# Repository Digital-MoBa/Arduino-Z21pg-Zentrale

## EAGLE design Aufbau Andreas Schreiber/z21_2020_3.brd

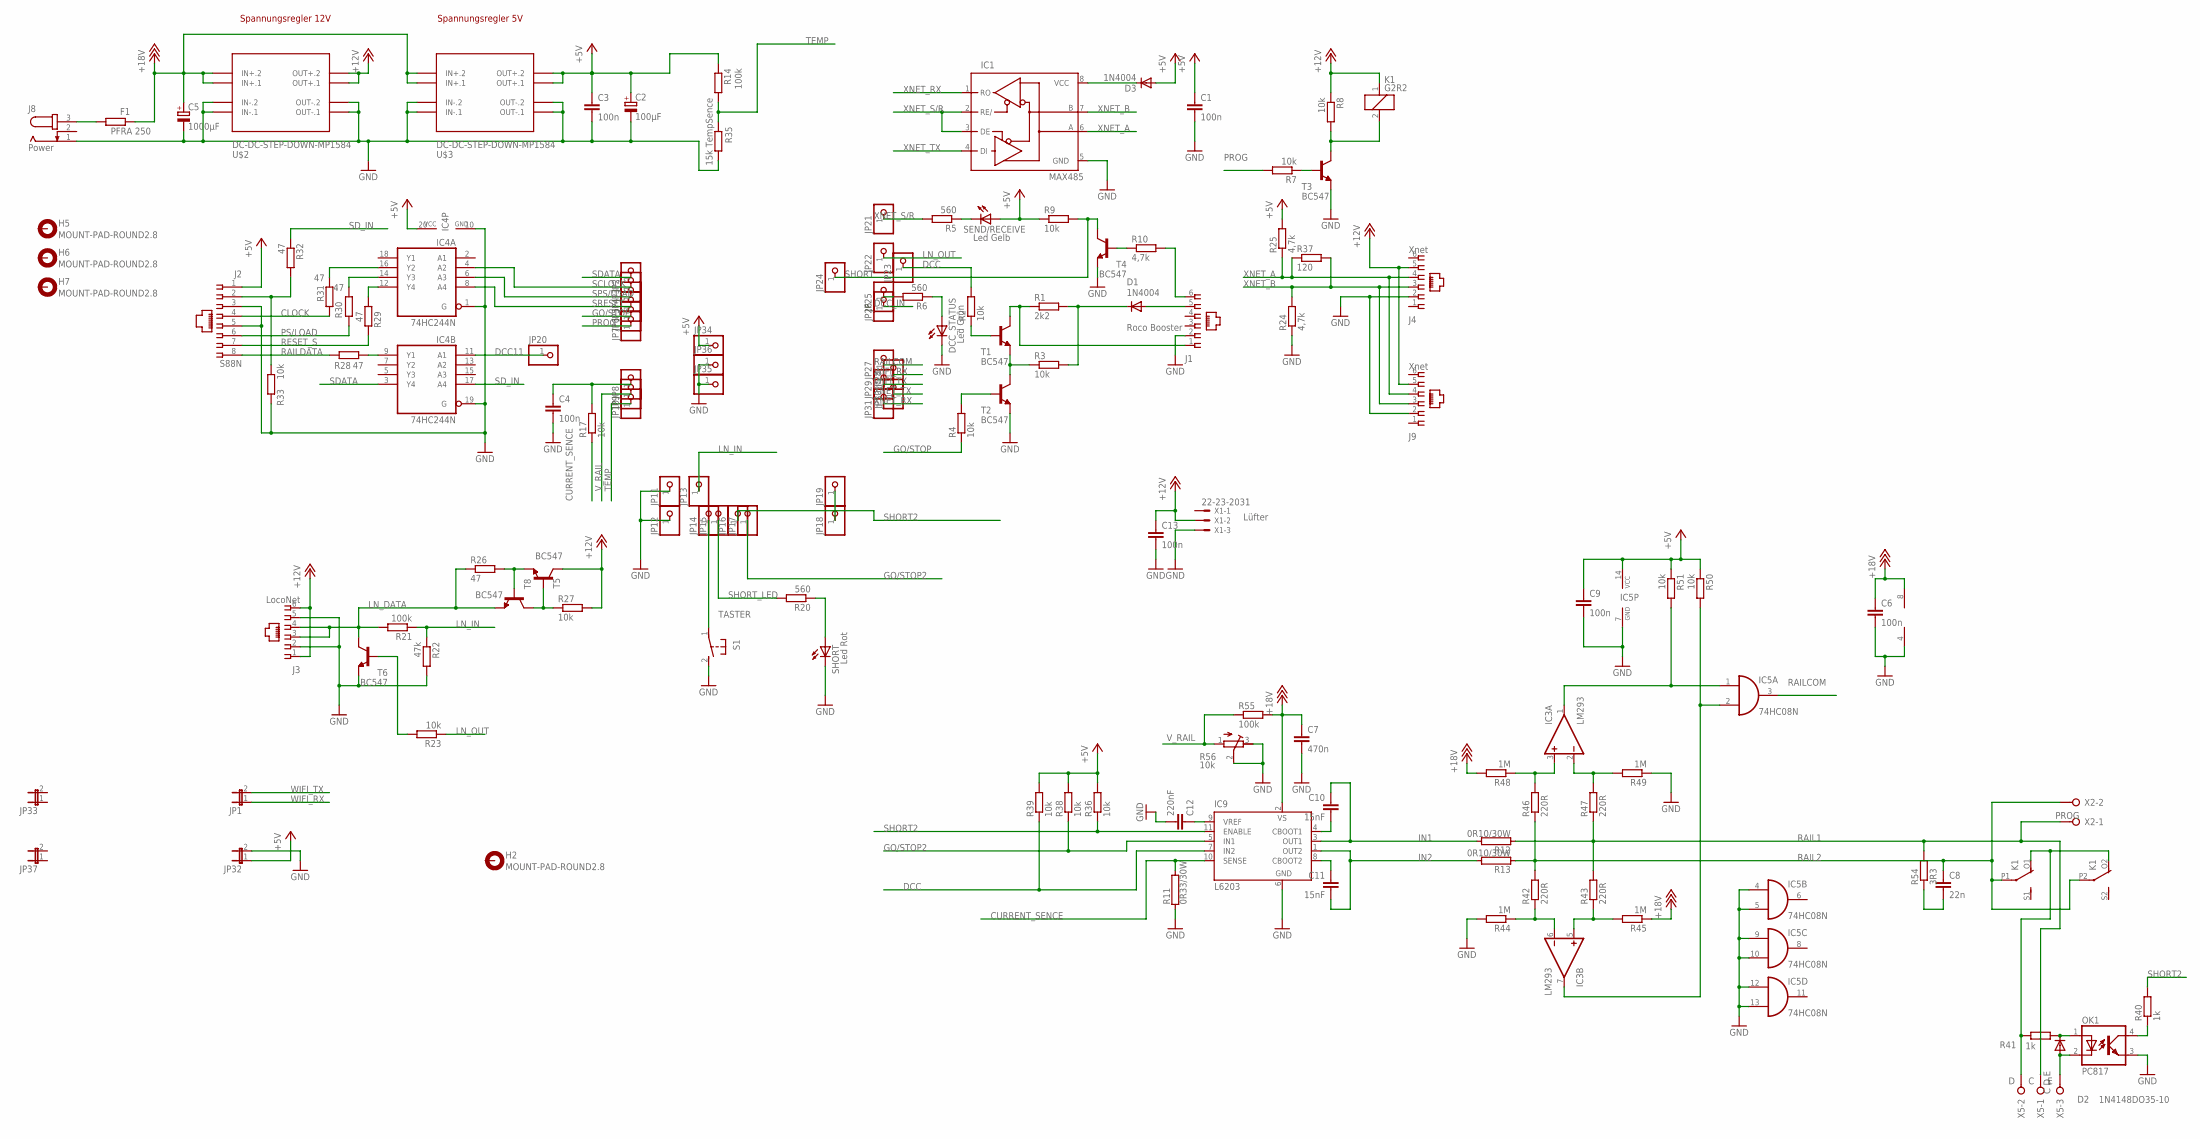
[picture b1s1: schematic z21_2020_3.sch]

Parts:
C1, C3, C4, C6, C9, C13: 100n; C050-024X044
C2: 100µF; E3,5-10
C5: 1000µF; E5-13
C7: 470n; C050-024X044
C8: 22n; C050-024X044
C10, C11: 15nF; C050-025X075
C12: 220nF; C050-025X075
D1, D3: 1N4004; DO41-10
D2: 1N4148DO35-10; DO35-10
DCC_STATUS: Led Grün; LD260
F1: PFRA 250; 0204/5
H2, H5, H6, H7: MOUNT-PAD-ROUND2.8; 2,8-PAD
IC1: MAX485; DIL08
IC3: LM293; DIL08
IC4: 74HC244N; DIL20
IC5: 74HC08N; DIL14
IC9: L6203; MULTIWATT-11
J1: Roco Booster; 520250-3
J2: S88N; 520251-4
J3: LocoNet; 520250-3
J4, J9: Xnet; 520250-3
J8: Power; SPC4077
JP1, JP32, JP33, JP37: JP1E; JP1
JP2, JP3, JP4, JP5, JP6, JP7, JP8, JP9, JP10, JP11, JP12, JP13, JP14, JP15, JP16, JP17, JP18, JP19, JP20, JP21, JP22, JP23, JP24, JP25, JP26, JP27, JP28, JP29, JP30, JP31, JP34, JP35, JP36: PINHD-1X1; 1X01
K1: G2R2
OK1: PC817; DIL04
R1: 2k2; 0204/7
R2: 10k; 0204/7
R3, R7, R8, R9, R17, R23, R27, R33, R36, R38, R39, R50, R51: 10k; 0207/10
R4: 10k; 0207/15
R5, R6, R20: 560; 0204/7
R10: 4,7k; 0204/7
R11: 0R33/30W; MNS-2
R12, R13: 0R10/30W; MNS-2
R14, R21: 100k; 0207/10
R22: 47k; 0207/10
R24, R25: 4,7k; 0207/10
R26: 47; 0204/7
R28, R29, R30, R31, R32: 47; 0207/10
R35: 15k TempSence; 0204/7
R37: 120; 0207/10
R40, R41: 1k; 0207/10
R42, R43, R46, R47: 220R; 0207/10
R44, R45, R48, R49: 1M; 0207/10
R54: 3R3; 0204/7
R55: 100k; 0207/12
R56: 10k; RTRIM64X
S1: 31-XX; B3F-31XX
SEND/RECEIVE: Led Gelb; LD260
SHORT: Led Rot; LD260
T1, T2, T3, T4, T5, T6, T8: BC547; TO92
U$2, U$3: DC-DC-STEP-DOWN-MP1584
X1: 22-23-2031
X2: PROG; W237-132
X5: C D E; W237-3E

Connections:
+5V: C1.1, C2.+, C3.1, C9.1, D3.A, IC4.20 (VCC), IC5.14 (VCC), J2.1, JP32.1, JP34.1, R9.1, R14.1, R25.2, R36.2, R38.2, R39.2, R50.1, R51.1, SEND/RECEIVE.A, U$3.OUT+.1, U$3.OUT+.2
+12V: C13.1, J3.1, J3.6, J4.5, J9.5, K1.1, R8.1, R27.2, T5.3 (C), U$2.OUT+.1, U$2.OUT+.2, X1.2
+18V: C5.+, C6.1, C7.1, F1.1, IC3.8 (V+), IC9.2 (VS), R45.1, R48.2, R55.2, U$2.IN+.1, U$2.IN+.2, U$3.IN+.1, U$3.IN+.2
CLOCK: J2.4, R31.2
CURRENT_SENCE: IC9.10 (SENSE), R11.2, R17.1
DCC: IC9.7 (IN2), JP23.1, R2.2, R39.1
DCC11: IC4.11 (A1), JP20.1
DCC_IN: JP26.1
GND: C1.2, C2.-, C3.2, C4.2, C5.-, C6.2, C7.2, C9.2, C12.2, C13.2, DCC_STATUS.K (C), IC1.5 (GND), IC3.4 (V-), IC4.1 (G), IC4.10 (GND), IC4.19 (G), IC5.4 (I0), IC5.5 (I1), IC5.7 (GND), IC5.9 (I0), IC5.10 (I1), IC5.12 (I0), IC5.13 (I1), IC9.6 (GND), J1.2, J2.3, J2.5, J3.2, J3.5, J4.2, J8.1, J9.2, JP11.1, JP12.1, JP32.2, JP35.1, JP36.1, OK1.3 (EMIT), R11.1, R22.2, R24.1, R33.2, R35.2, R44.2, R49.1, R56.2 (S), R56.3 (E), S1.2 (S), SHORT.K (C), T2.1 (E), T3.1 (E), T4.1 (E), T6.1 (E), U$2.IN-.1, U$2.IN-.2, U$2.OUT-.1, U$2.OUT-.2, U$3.IN-.1, U$3.IN-.2, U$3.OUT-.1, U$3.OUT-.2, X1.3
GO/STOP: JP6.1, R4.1
GO/STOP2: IC9.5 (IN1), JP17.1, R38.1
IN1: C10.1, IC9.3 (OUT1), R12.2
IN2: C11.2, IC9.1 (OUT2), R13.2
LN_DATA: J3.3, J3.4, R21.2, R26.1, T6.3 (C), T8.1 (E)
LN_IN: JP13.1, R21.1, R22.1
LN_OUT: JP22.1, R23.1
unnamed: J1.6, R10.2
unnamed: D1.C, R1.2, R3.2
unnamed: D1.A, J1.5
unnamed: R2.1, T1.2 (B)
unnamed: R3.1, T1.1 (E), T2.3 (C)
unnamed: J1.1, R1.1, T1.3 (C)
unnamed: JP25.1, R6.2
unnamed: F1.2, J8.3
unnamed: R4.2, T2.2 (B)
unnamed: DCC_STATUS.A, R6.1
unnamed: R5.1, SEND/RECEIVE.K (C)
unnamed: D3.C, IC1.8 (VCC)
unnamed: K1.2, R8.2, T3.3 (C)
unnamed: R7.1, T3.2 (B)
unnamed: R10.1, T4.2 (B)
unnamed: JP18.1, JP19.1
unnamed: R20.1, SHORT.A
unnamed: C4.1, JP8.1, R17.2
unnamed: K1.O1 (O), K1.O2 (O), R41.2, X5.2
unnamed: D2.C, OK1.1 (A), R41.1
unnamed: R26.2, T5.1 (E), T8.2 (B)
unnamed: R23.2, T6.2 (B)
unnamed: D2.A, OK1.2 (C), X5.3
unnamed: R27.1, T5.2 (B), T8.3 (C)
unnamed: IC4.9 (Y1), R28.2
unnamed: IC4.14 (Y3), R30.1
unnamed: IC4.16 (Y2), R31.1
unnamed: IC4.12 (Y4), R29.1
unnamed: IC3.6 (-IN), R42.1, R44.1
unnamed: J2.2, R32.2, R33.1
unnamed: IC3.5 (+IN), R43.1, R45.2
unnamed: IC3.7 (OUT), IC5.2 (I1), R50.2
unnamed: IC3.3 (+IN), R46.2, R48.1
unnamed: IC3.2 (-IN), R47.2, R49.2
unnamed: OK1.4 (COL), R40.1
unnamed: IC3.1 (OUT), IC5.1 (I0), R51.2
unnamed: C10.2, IC9.4 (CBOOT1)
unnamed: C8.2, R54.1
unnamed: C11.1, IC9.8 (CBOOT2)
unnamed: C12.1, IC9.9 (VREF)
PROG: JP7.1, R7.2
PS/LOAD: J2.6, R30.2
RAIL1: R12.1, R43.2, R47.1, R54.2, X2.1, X5.1
RAIL2: C8.1, K1.P1, K1.P2, R13.1, R42.2, R46.1, X2.2
RAILCOM: IC5.3 (O), JP27.1
RAILDATA: J2.8, R28.1
RESET_S: J2.7, R29.2
SCLOCK: IC4.4 (A2), JP3.1
SDATA: IC4.3 (Y4), JP2.1
SD_IN: IC4.17 (A4), R32.1
SHORT: JP24.1, R9.2, T4.3 (C)
SHORT2: IC9.11 (ENABLE), JP16.1, R36.1, R40.2
SHORT_LED: JP15.1, R20.2
SPS/LOAD: IC4.6 (A3), JP4.1
SRESET: IC4.8 (A4), JP5.1
TASTER: JP14.1, S1.1
TEMP: JP10.1, R14.2, R35.1
V_RAIL: JP9.1, R55.1, R56.1 (A)
WIFI_RX: JP1.1, JP28.1
WIFI_TX: JP1.2, JP29.1
XNET_A: IC1.6 (A), J4.4, J9.4, R25.1, R37.1
XNET_B: IC1.7 (B), J4.3, J9.3, R24.2, R37.2
XNET_RX: IC1.1 (RO), JP31.1
XNET_S/R: IC1.2 (RE/), IC1.3 (DE), JP21.1, R5.2
XNET_TX: IC1.4 (DI), JP30.1

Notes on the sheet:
Spannungsregler 12V
Spannungsregler 5V
D C E
Lüfter

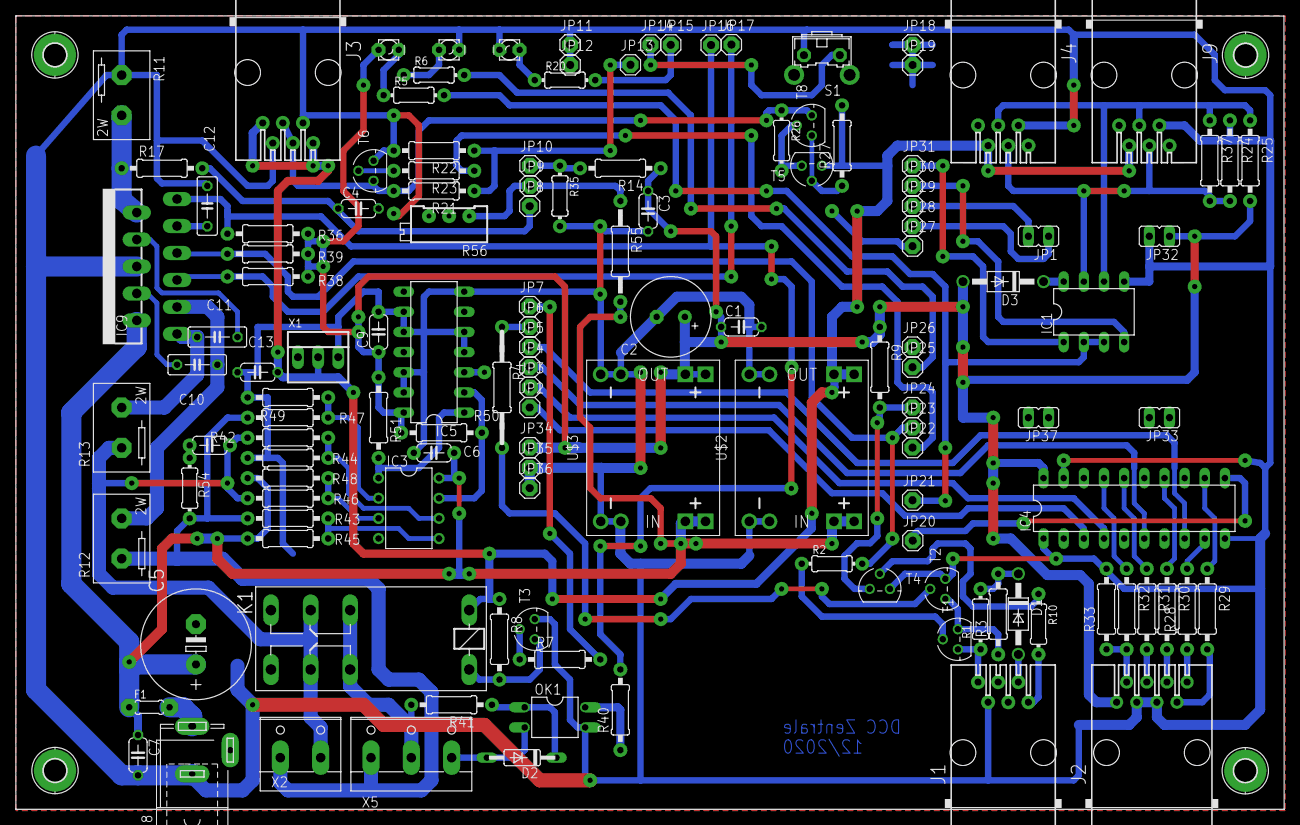
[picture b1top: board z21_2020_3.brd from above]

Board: 2 copper layers, 159.9 x 100.0 mm, 136 parts (0 on the bottom side), 80 nets.

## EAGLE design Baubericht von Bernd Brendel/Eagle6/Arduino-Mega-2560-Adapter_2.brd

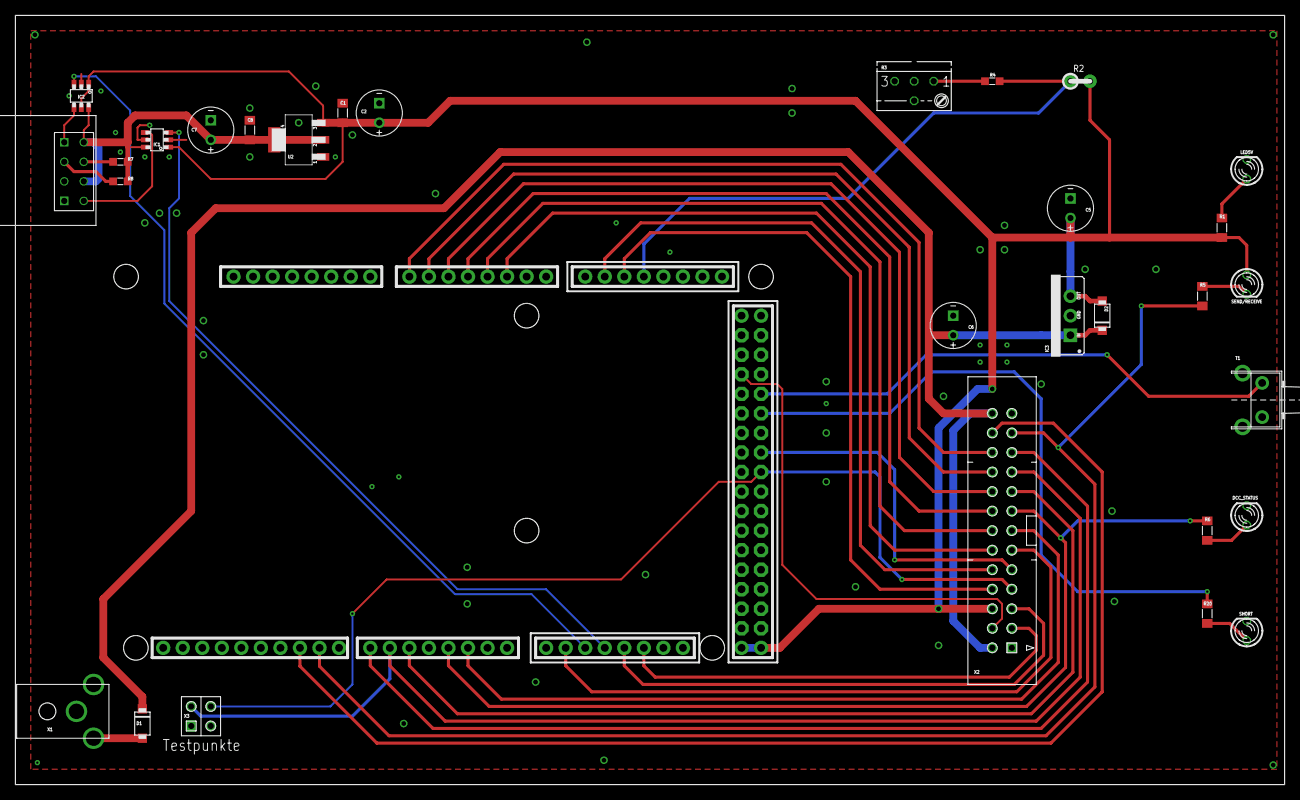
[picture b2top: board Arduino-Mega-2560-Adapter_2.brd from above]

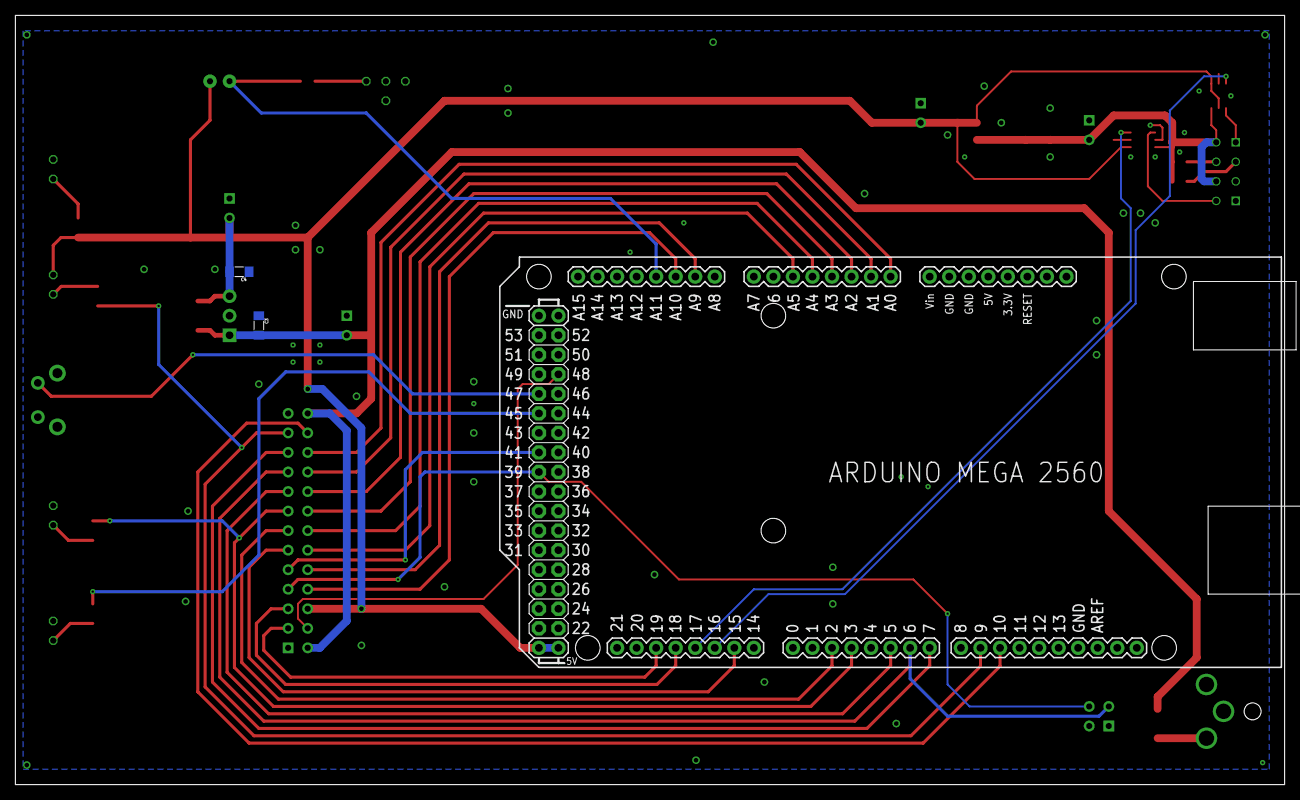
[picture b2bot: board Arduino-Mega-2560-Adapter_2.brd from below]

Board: 2 copper layers, 165.0 x 100.0 mm, 33 parts (3 on the bottom side), 40 nets.

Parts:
C1, C3, C4, C8: 1µ; C0805
C2, C5, C6, C7: 100µ; RM2.5_DIA6
D1, D2: SS14L; SUB-SMA_
DCC_STATUS: LED3MM_
IC1, IC2: 74LVC1T45; SOT23-6_
IC3: DC/DC_5V; 78XXS
LED5V: LED3MM_
PCB1: ARDUINO_MEGA2560
R1, R5, R6, R20: 470R; R0805
R2: TempSens.; RM02,5
R3: 50k; S64YW
R4, R7, R8: 10k; R0603
SEND/RECEIVE: LED3MM_
SHORT: LED3MM_
T1: TACT6060-90°; TACT6060-90°_
U2: 1117-3,3; SOT223__
WIFI: ESP01
X1: DCBU2,1-PRNB
X2: 2X13_WANNE_180°
X3: 2X02_2.54MM

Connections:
+3V3: C7.PLUS, C8.2, IC1.6, IC2.6, R7.P$1, R8.P$1, U2.2, U2.4, WIFI.CH_PD, WIFI.VCC
+5V: C1.2, C2.PLUS, C4.2, C5.PLUS, D2.A, IC1.1, IC2.1, IC2.5, IC3.OUT, PCB1.5V., PCB1.5V.., R1.P$2, R2.P$2, SEND/RECEIVE.A, U2.3, X2.P$6
CS: PCB1.10, X2.P$24
CURRENT_SENSE: PCB1.A9, X2.P$10
DCC: PCB1.6, X2.P$19, X3.P$2
DCC_IN: PCB1.2, X2.P$13
DCC_STATUS: PCB1.3, R6.P$2, X2.P$15
GND: C1.1, C2.MINUS, C3.1, C4.1, C5.MINUS, C6.MINUS, C7.MINUS, C8.1, DCC_STATUS.K, IC1.2, IC1.5, IC2.2, IC3.GND, LED5V.K, PCB1.GND, PCB1.GND., PCB1.GND.., PCB1.GND..., PCB1.GND...., R3.E, R3.S, R3.S@1, SHORT.K, T1.1, T1.3, T1.4, U2.1, WIFI.GND, X1.AUßEN, X1.ÖFFNER, X2.P$1, X2.P$25, X3.P$1, X3.P$3
GO/STOP: PCB1.A4, X2.P$14
GO/STOP2: PCB1.39, X2.P$7, X3.P$4
LN_OUT: PCB1.7, X2.P$21
LN_RECEIVE: PCB1.48, X2.P$4
unnamed: R7.P$2, WIFI.RST
unnamed: R5.P$2, SEND/RECEIVE.K
unnamed: DCC_STATUS.A, R6.P$1
unnamed: R20.P$1, SHORT.A
unnamed: LED5V.A, R1.P$1
unnamed: R8.P$2, WIFI.GPIO0
unnamed: C3.2, C6.PLUS, D1.K, D2.K, IC3.IN, X2.P$2, X2.P$26
unnamed: D1.A, X1.INNEN
unnamed: R3.A, R4.P$1
PROG: PCB1.A5, X2.P$12
RAILCOM: PCB1.15, X2.P$11
SCLOCK: PCB1.A1, X2.P$20
SDATA: PCB1.A0, X2.P$22
SHORT: PCB1.5, X2.P$17
SHORT2: PCB1.41, X2.P$9
SHORT_LED: PCB1.45, R20.P$2
SPS/LOAD: PCB1.A2, X2.P$18
SRESET: PCB1.A3, X2.P$16
TASTER: PCB1.47, T1.2
TEMP: PCB1.A11, R2.P$1, R4.P$2
V_RAIL: PCB1.A10, X2.P$8
WIFI_RX: IC2.3, PCB1.16
WIFI_RX3: IC2.4, WIFI.RX
WIFI_TX: IC1.3, PCB1.17
WIFI_TX3: IC1.4, WIFI.TX
XNET_RX: PCB1.19, X2.P$3
XNET_S/R: PCB1.9, R5.P$1, X2.P$23
XNET_TX: PCB1.18, X2.P$5

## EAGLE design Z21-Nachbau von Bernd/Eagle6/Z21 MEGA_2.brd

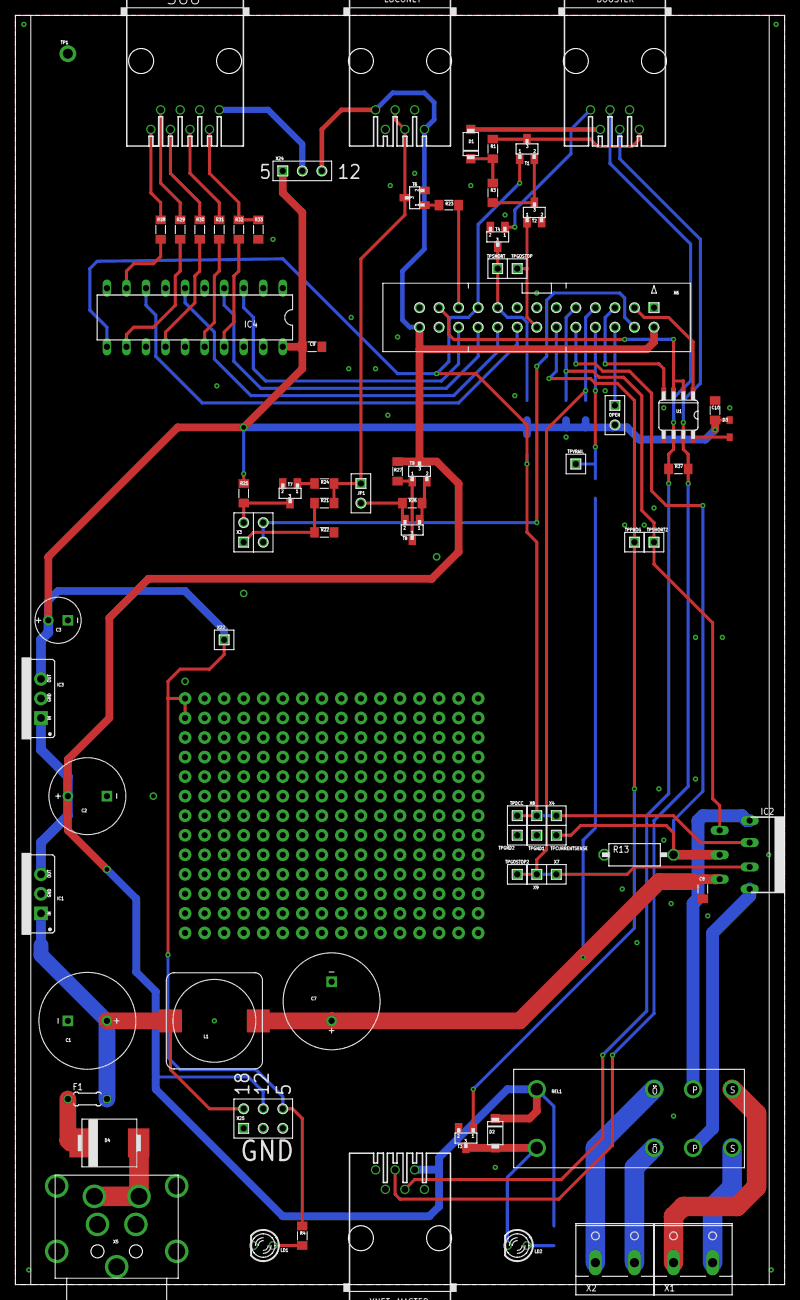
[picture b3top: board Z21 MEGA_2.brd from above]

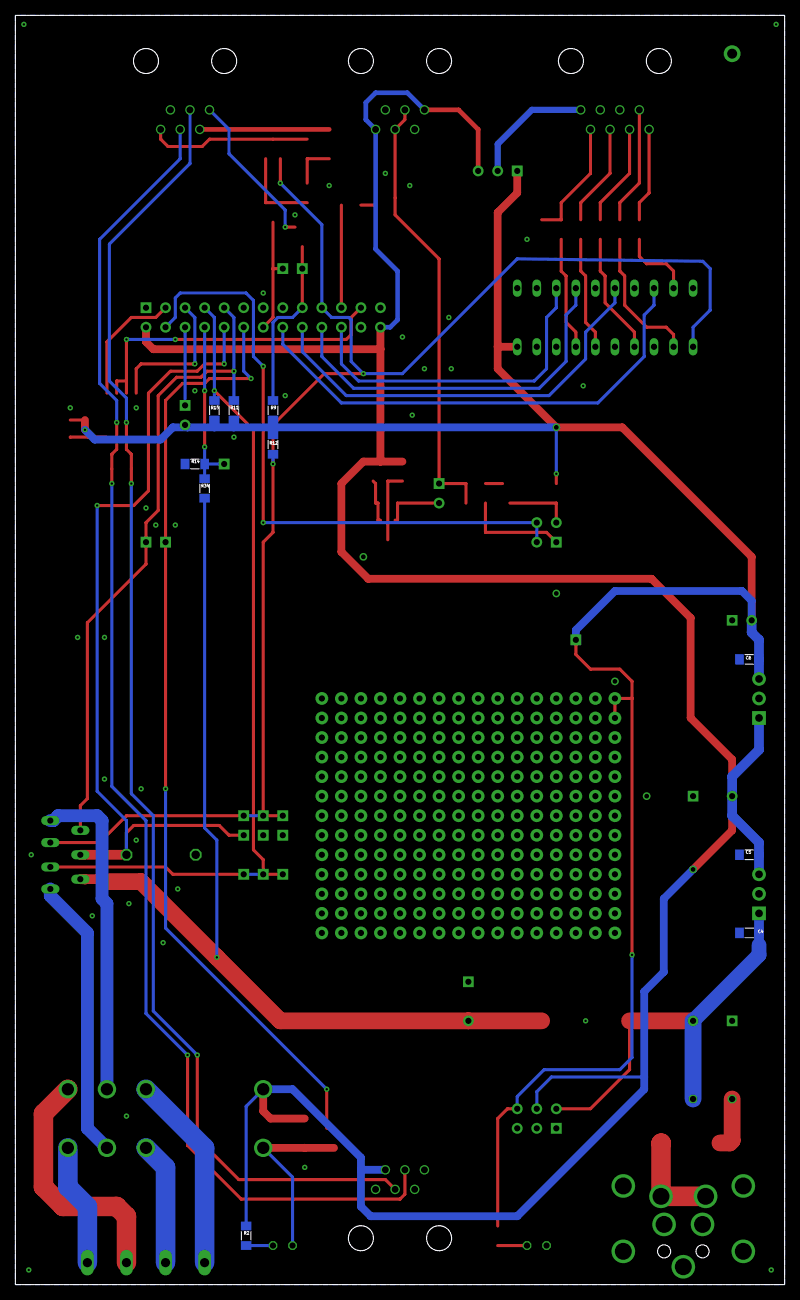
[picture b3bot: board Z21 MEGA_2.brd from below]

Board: 2 copper layers, 100.0 x 165.0 mm, 86 parts (10 on the bottom side), 61 nets.

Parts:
BOOSTER: 520250-3
C1, C7: 1000µ; RM5_DIA12.5
C2: 470µ; RM5_DIA10
C3: 100µ; RM2.5_DIA6
C4, C8: 1µ/50V; C0805
C5, C6: 1µ; C0805
C9, C10: 100n; C0805
D1, D2: SS14L; SUB-SMA_
D3: 1N4148; SOD323_
D4: SK86; SMC_
F1: 4A; 0204/5
IC1: 7812; 78XXS
IC2: TLE5206-2; P-TO220-7-11
IC3: 7805; 78XXS
IC4: 74HC244N; DIL20
JP1: 1X02_JUMPER_2.54MM; 1X02_2.54MM
L1: 10µH/5,4A; 12,5X12,5MM
LD1: gn; LED3MM_
LD2: ge; LED3MM_
LOCONET: 520250-3
OPEN: 1X02_JUMPER_2.54MM; 1X02_2.54MM
R1: 2,2k; R0805
R2, R14: 4,7k; R0805
R3, R9, R11, R12, R15, R24, R27, R33: 10k; R0805
R4: 1k; R0805
R13: 0R33 5W; VMTA55
R21, R23, R34: 100k; R0805
R22: 47k; R0805
R25: 470R; R0805
R26, R28, R29, R30, R31, R32: 47R; R0805
R37: n.m.; R0805
REL1: DIL16_1FINDER_40.527; FINDER_40.527
S88: 520251-4
T1, T2, T3, T4: PDTC143ZT; SOT23_
T6, T7, T8, T9: BC847; SOT23_
TP1: LÖTPUNKTTHT_1.3MM_51.2MIL; THT_1.3MM_51.2MIL
TPCURRENTSENSE: 1X01_2.54MM
TPDCC: 1X01_2.54MM
TPGND1, TPGND2: 1X01_2.54MM
TPGOSTOP, TPGOSTOP2: 1X01_2.54MM
TPPROG: 1X01_2.54MM
TPSHORT, TPSHORT2: 1X01_2.54MM
TPVRAIL: 1X01_2.54MM
U1: SP485; SO8__
X1: PROG OUT; W237-132
X2: TRACK OUT; W237-132
X3: 2X02_2.54MM
X4, X7, X8, X9, X22: 1X01_2.54MM
X5: MDINBU4-POWER
X6: 2X13_WANNE_180°
X24: 1X03_2.54MM
X25: 2X03_2.54MM
XNET-MASTER: 520250-3

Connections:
+5V: C3.PLUS, C6.2, C9.2, C10.2, D3.ANODE, IC3.OUT, IC4.20, OPEN.P$2, R4.P$2, R9.P$2, R11.P$2, R12.P$2, R15.P$2, R25.P$2, X22.P$1, X24.P$1, X25.P$6
+12V: C2.PLUS, C5.2, D2.K, IC1.OUT, IC3.IN, LOCONET.1, LOCONET.6, R2.P$2, R27.P$2, REL1.SP1, T9.3, X6.P$2, X6.P$26, X24.P$3, X25.P$4, XNET-MASTER.5
+18V: C1.PLUS, C4.2, F1.1, IC1.IN, L1.P$2, X25.P$2
CLOCK: R31.P$1, S88.4
CURRENT_SENSE: IC2.4, R13.1, TPCURRENTSENSE.P$1, X6.P$10
DCC: IC2.3, IC4.11, R12.P$1, T1.1, TPDCC.P$1, X4.P$1, X6.P$19, X8.P$1
GND: BOOSTER.2, C1.MINUS, C2.MINUS, C3.MINUS, C4.1, C5.1, C6.1, C7.MINUS, C8.2, C9.1, C10.1, IC1.GND, IC3.GND, IC4.1, IC4.2, IC4.10, IC4.13, IC4.15, IC4.19, LD1.K, LOCONET.2, LOCONET.5, R13.2, R14.P$1, R22.P$1, R33.P$2, S88.3, S88.5, T2.2, T3.2, T4.2, T6.2, T7.2, TP1.P$1, TPGND1.P$1, TPGND2.P$1, U1.5, X5.3, X5.4, X6.P$1, X6.P$25, X25.P$1, X25.P$3, X25.P$5, XNET-MASTER.2
GO/STOP: T2.1, TPGOSTOP.P$1, X6.P$14
GO/STOP2: IC2.5, R15.P$1, TPGOSTOP2.P$1, X6.P$7, X7.P$1, X9.P$1
LN_DATA: JP1.P$1, LOCONET.3, LOCONET.4, R21.P$1, R24.P$1, T6.3
LN_IN: R21.P$2, R22.P$2, X3.P$1
LN_OUT: R23.P$2, X6.P$21
LN_RECEIVE: X3.P$3, X3.P$4, X6.P$4
unnamed: OPEN.P$1, X6.P$6
unnamed: D1.K, R1.P$2, R3.P$2
unnamed: IC2.7, REL1.P1
unnamed: IC2.1, REL1.P2
unnamed: R3.P$1, T1.2, T2.3
unnamed: REL1.Ö2, X2.1
unnamed: D4.K, F1.2
unnamed: D4.A, X5.1, X5.2
unnamed: C7.PLUS, C8.1, IC2.6, L1.P$1, R34.P$2
unnamed: D3.KATHODE, U1.8
unnamed: D2.A, LD2.K, REL1.SP2, T3.3
unnamed: REL1.Ö1, X2.2
unnamed: REL1.S2, X1.1
unnamed: REL1.S1, X1.2
unnamed: R26.P$2, T8.1, T9.2
unnamed: R23.P$1, T6.1
unnamed: R24.P$2, T7.1
unnamed: R27.P$1, T8.3, T9.1
unnamed: IC4.9, R28.P$2
unnamed: IC4.14, R30.P$2
unnamed: IC4.16, R31.P$2
unnamed: IC4.12, R29.P$2
unnamed: R32.P$2, R33.P$1, S88.2
unnamed: JP1.P$2, R26.P$1, T8.2
unnamed: S88.1, X24.P$2
unnamed: BOOSTER.6, T4.1
unnamed: BOOSTER.1, R1.P$1, T1.3
unnamed: LD2.A, R2.P$1
unnamed: LD1.A, R4.P$1
unnamed: R25.P$1, T7.3, X3.P$2
unnamed: BOOSTER.5, D1.A
PROG: T3.1, TPPROG.P$1, X6.P$12
PS/LOAD: R30.P$1, S88.6
RAILDATA: R28.P$1, S88.8
RESET_S: R29.P$1, S88.7
SCLOCK: IC4.4, X6.P$20
SDATA: IC4.3, X6.P$22
SD_IN: IC4.17, R32.P$1
SHORT: R9.P$1, T4.3, TPSHORT.P$1, X6.P$17
SHORT2: IC2.2, R11.P$1, TPSHORT2.P$1, X6.P$9
SPS/LOAD: IC4.6, X6.P$18
SRESET: IC4.8, X6.P$16
V_RAIL: R14.P$2, R34.P$1, TPVRAIL.P$1, X6.P$8
XNET_A: BOOSTER.4, R37.P$1, U1.6, XNET-MASTER.4
XNET_B: BOOSTER.3, R37.P$2, U1.7, XNET-MASTER.3
XNET_RX: U1.1, X6.P$3
XNET_S/R: U1.2, U1.3, X6.P$23
XNET_TX: U1.4, X6.P$5

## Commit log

2021-04-14 Set theme jekyll-theme-architect

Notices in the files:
parts and their libraries:
diy-modules: Released under the Creative Commons Attribution 4.0 International License: http://creativecommons.org/licenses/by/4.0
